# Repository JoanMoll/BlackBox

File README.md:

# BlackBox — Room Health / Environmental Monitoring PCB

Custom KiCad PCB for a battery-powered, ESP32-class device intended to monitor room/environment conditions and log data locally.

## Design previews

### 3D view

### PCB layout

### Schematic

## Project overview
BlackBox is a hardware design project focused on a practical embedded system that combines sensing, local storage, battery operation, and an ESP32-class MCU. The goal is a compact “room health” monitoring unit that can collect measurements and store them for later analysis.

## Intended system (high-level)
- MCU / Wireless: ESP32-class microcontroller (e.g., ESP32-S3)
- Sensors: LDR (ambient light), ultrasonic (distance/proximity), plus analog sensor input(s)
- Analog front-end: LMV321 op-amp stage for signal conditioning/amplification
- Storage: micro-SD card for local data logging
- Power: battery input (VBAT) with 3.3 V regulation and battery management/protection

## Repository contents
- KiCad project: `.kicad_pro`
- Schematic: `.kicad_sch`
- PCB layout: `.kicad_pcb`
- 3D model export: `.step` (if included)
- Documentation images: `docs/pcb_3d.png`, `docs/pcb_layout.png`, `docs/schematic.png`

## How to open and review
1. Install KiCad (v7+ recommended).
2. Open the `.kicad_pro` file.
3. Review the schematic (`.kicad_sch`) and PCB layout (`.kicad_pcb`).
4. Run ERC (schematic checks) and DRC (PCB checks) inside KiCad.

## Status
- Schematic and PCB layout created
- Next: final DRC/ERC pass and documentation polish
- Next: order PCB and bring-up tests (power rails, SD, sensor IO)
- Next: firmware (sampling + logging format) and enclosure design

## Skills demonstrated
- End-to-end PCB design workflow in KiCad (schematic capture, layout, manufacturable design)
- Embedded hardware system design (power, sensing, analog conditioning, storage interfaces)
- Clear engineering documentation for review (renders + structured project summary)

## License
If no license file is included, all rights reserved (portfolio viewing only).

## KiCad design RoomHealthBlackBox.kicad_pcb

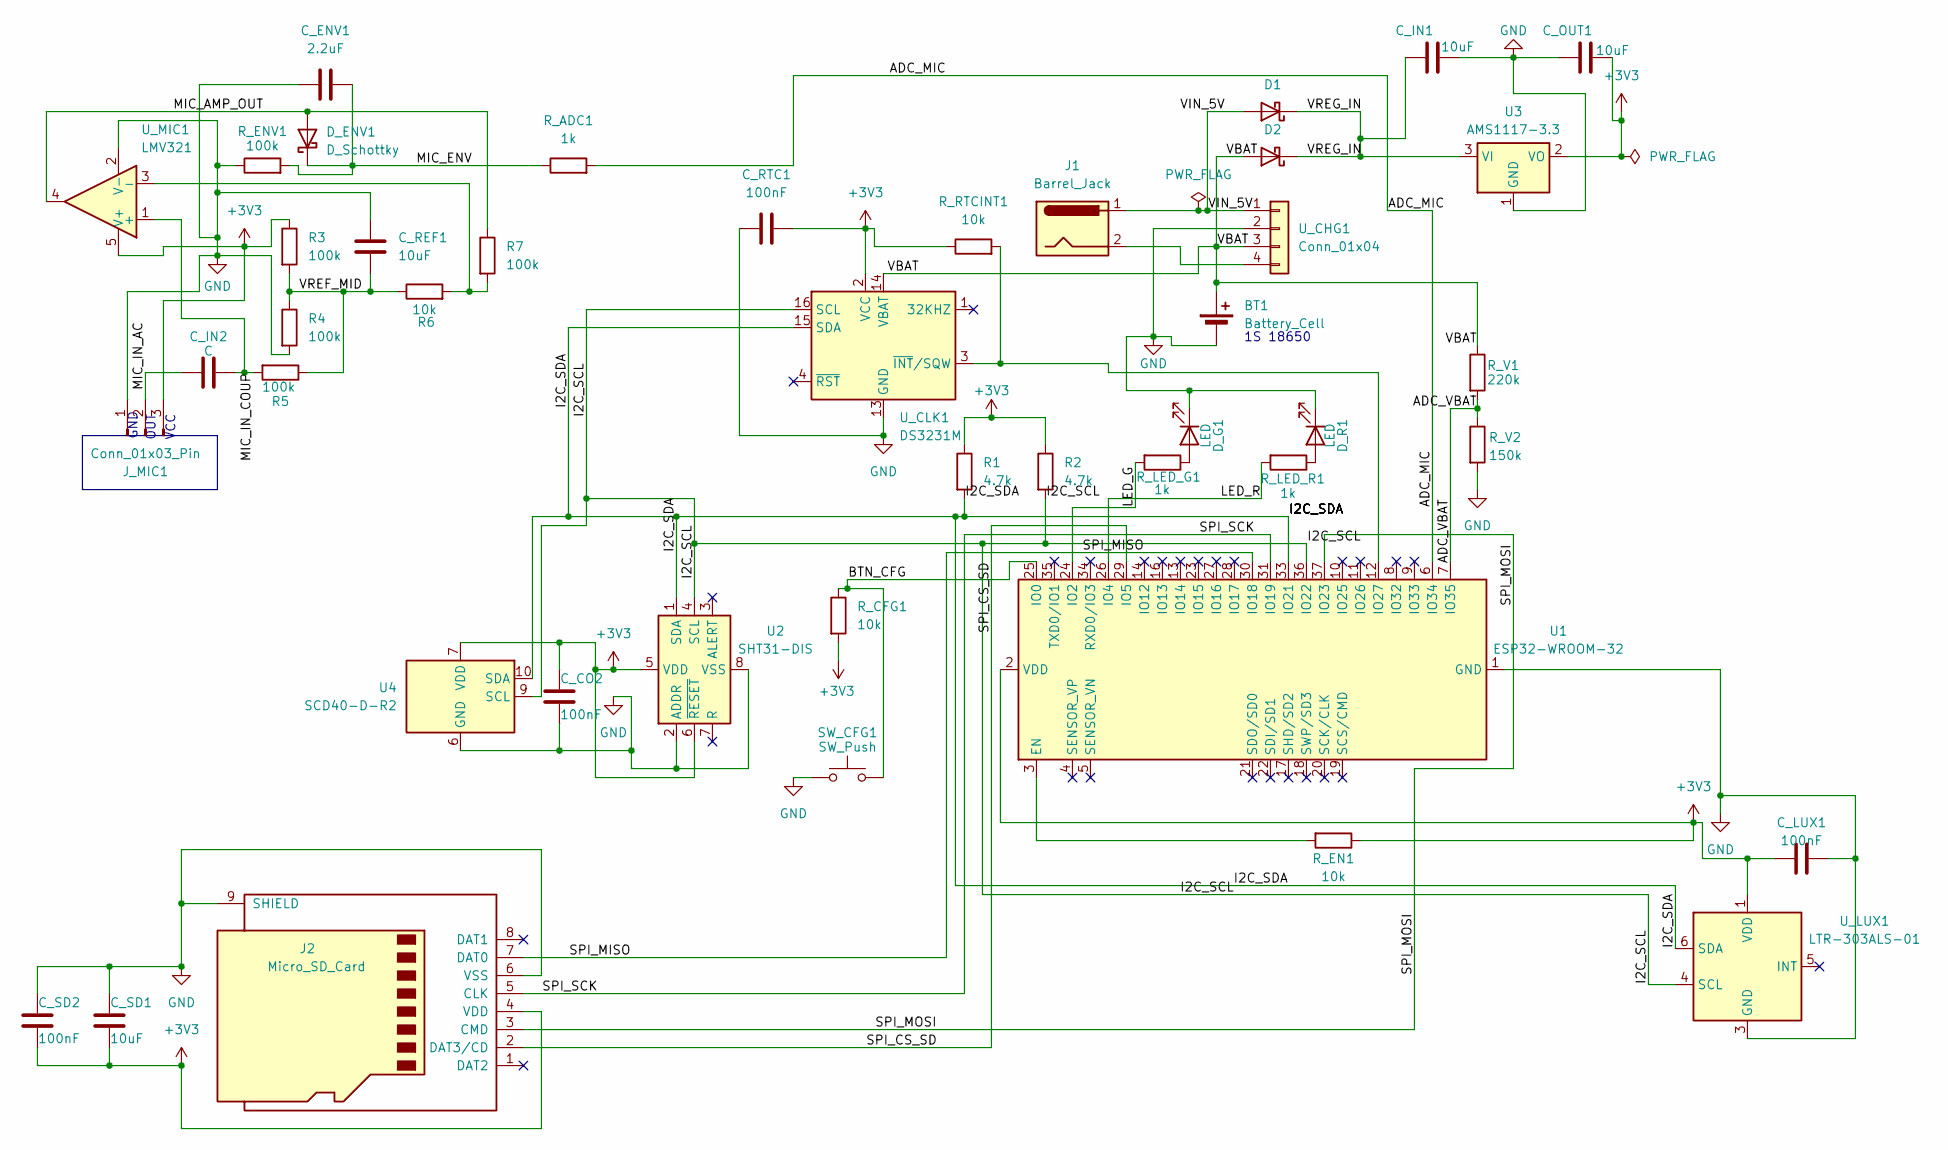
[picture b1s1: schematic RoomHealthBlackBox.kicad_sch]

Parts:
BT1: Battery_Cell; BatteryHolder_MPD_BH-18650-PC
C_CO2: 100nF; C_0201_0603Metric
C_ENV1: 2.2uF; C_0201_0603Metric
C_IN1: 10uF; C_0201_0603Metric
C_IN2: C; C_0201_0603Metric
C_LUX1: 100nF; C_0201_0603Metric
C_OUT1: 10uF; C_0201_0603Metric
C_REF1: 10uF; C_0201_0603Metric
C_RTC1: 100nF; C_0201_0603Metric
C_SD1: 10uF; C_0201_0603Metric
C_SD2: 100nF; C_0201_0603Metric
D1, D2: D_Schottky; D_0201_0603Metric
D_ENV1: D_Schottky; D_0201_0603Metric
D_G1: LED; LED_0201_0603Metric
D_R1: LED; LED_0201_0603Metric
J1: Barrel_Jack; BarrelJack_Horizontal
J2: Micro_SD_Card; microSD_HC_Molex_104031-0811
J_MIC1: Conn_01x03_Pin; PinHeader_1x04_P2.54mm_Vertical
R1, R2: 4.7k; R_0201_0603Metric
R3, R4, R5, R7: 100k; R_0201_0603Metric
R6: 10k; R_0201_0603Metric
R_ADC1: 1k; R_0201_0603Metric
R_CFG1: 10k; R_0201_0603Metric
R_EN1: 10k; R_0201_0603Metric
R_ENV1: 100k; R_0201_0603Metric
R_LED_G1: 1k; R_0201_0603Metric
R_LED_R1: 1k; R_0201_0603Metric
R_RTCINT1: 10k; R_0201_0603Metric
R_V1: 220k; R_0201_0603Metric
R_V2: 150k; R_0201_0603Metric
SW_CFG1: SW_Push; SW_SPST_PTS645Sx43SMTR92
U1: ESP32-WROOM-32
U2: SHT31-DIS; Sensirion_DFN-8-1EP_2.5x2.5mm_P0.5mm_EP1.1x1.7mm
U3: AMS1117-3.3; SOT-223-3_TabPin2
U4: SCD40-D-R2; Sensirion_SCD4x-1EP_10.1x10.1mm_P1.25mm_EP4.8x4.8mm
U_CHG1: Conn_01x04; PinHeader_1x04_P2.54mm_Vertical
U_CLK1: DS3231M; SOIC-16W_7.5x10.3mm_P1.27mm
U_LUX1: LTR-303ALS-01; Lite-On_LTR-303ALS-01
U_MIC1: LMV321; SOT-23-5

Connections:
+3V3: C_CO2.1, C_LUX1.1, C_OUT1.2, C_RTC1.2, C_SD1.2, C_SD2.2, J2.4 (VDD), J_MIC1.3, R1.1, R2.1, R3.1, R_CFG1.2, R_EN1.1, R_RTCINT1.1, U1.2 (VDD), U2.5 (VDD), U2.6 (~RESET), U3.2 (VO), U4.7 (VDD), U4.19 (VDD), U_CLK1.2 (VCC), U_LUX1.1 (VDD), U_MIC1.5 (V+)
/ADC_MIC: R_ADC1.2, U1.6 (IO34)
/ADC_VBAT: R_V1.2, R_V2.1, U1.7 (IO35)
/BTN_CFG: R_CFG1.1, SW_CFG1.2, U1.25 (IO0)
/I2C_SCL: R2.2, U1.36 (IO22), U2.4 (SCL), U4.9 (SCL), U_CLK1.16 (SCL), U_LUX1.4 (SCL)
/I2C_SDA: R1.2, U1.33 (IO21), U2.1 (SDA), U4.10 (SDA), U_CLK1.15 (SDA), U_LUX1.6 (SDA)
/LED_G: R_LED_G1.2, U1.24 (IO2)
/LED_R: R_LED_R1.2, U1.26 (IO4)
/MIC_AMP_OUT: D_ENV1.2 (A), R7.1, U_MIC1.4
/MIC_ENV: C_ENV1.2, D_ENV1.1 (K), R_ADC1.1, R_ENV1.2
/MIC_IN_AC: C_IN2.2, J_MIC1.2
/MIC_IN_COUP: C_IN2.1, R5.2, U_MIC1.1 (+)
/SPI_CS_SD: J2.2 (DAT3/CD), U1.29 (IO5)
/SPI_MISO: J2.7 (DAT0), U1.30 (IO18)
/SPI_MOSI: J2.3 (CMD), U1.37 (IO23)
/SPI_SCK: J2.5 (CLK), U1.31 (IO19)
/VBAT: BT1.1 (+), D2.2 (A), R_V1.1, U_CHG1.3, U_CLK1.14 (VBAT)
/VIN_5V: D1.2 (A), J1.1, U_CHG1.1
/VREF_MID: C_REF1.2, R3.2, R4.1, R5.1, R6.1
/VREG_IN: C_IN1.2, D1.1 (K), D2.1 (K), U3.3 (VI)
GND: BT1.2 (-), C_CO2.2, C_ENV1.1, C_IN1.1, C_LUX1.2, C_OUT1.1, C_REF1.1, C_RTC1.1, C_SD1.1, C_SD2.1, D_G1.1 (K), D_R1.1 (K), J2.6 (VSS), J2.9 (SHIELD), J_MIC1.1, R4.2, R_ENV1.1, R_V2.2, SW_CFG1.1, U1.1 (GND), U1.15 (GND), U1.38 (GND), U1.39 (GND), U2.2 (ADDR), U2.8 (VSS), U2.9 (VSS), U3.1 (GND), U4.6 (GND), U4.20 (GND), U4.21 (GND), U_CHG1.2, U_CLK1.5 (GND), U_CLK1.6 (GND), U_CLK1.7 (GND), U_CLK1.8 (GND), U_CLK1.9 (GND), U_CLK1.10 (GND), U_CLK1.11 (GND), U_CLK1.12 (GND), U_CLK1.13 (GND), U_LUX1.3 (GND), U_MIC1.2 (V-)
unnamed: D_G1.2 (A), R_LED_G1.1
unnamed: D_R1.2 (A), R_LED_R1.1
unnamed: R_EN1.2, U1.3 (EN)
unnamed: R_RTCINT1.2, U1.12 (IO27), U_CLK1.3 (~INT/SQW)
unnamed: J1.2, U_CHG1.4
unnamed: R6.2, R7.2, U_MIC1.3 (-)

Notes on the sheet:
OUT
GND
1S 18650
VCC

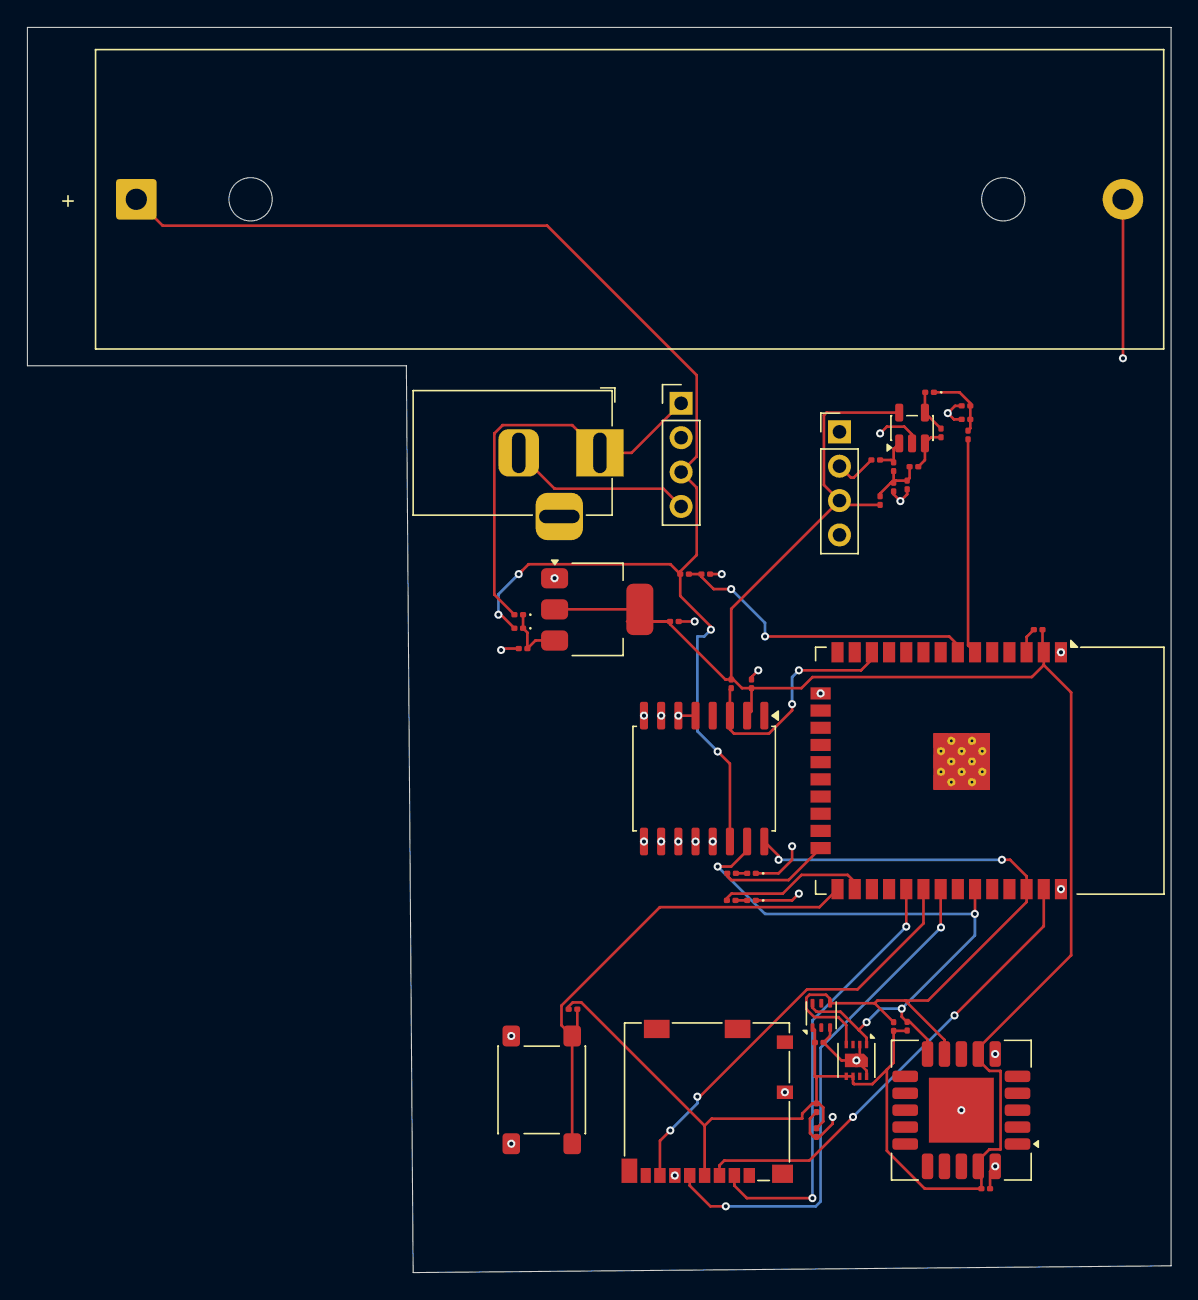
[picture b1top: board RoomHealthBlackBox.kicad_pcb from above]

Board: 2 copper layers, 84.5 x 92.0 mm, 44 parts (0 on the bottom side), 27 nets.

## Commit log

2026-02-19 Create README for BlackBox environmental monitoring device
    Added README.md with project overview and details.
2026-02-19 Clean repo structure: docs and fab, remove backups
2026-02-19 Remove backups, png exports, and report
2026-02-19 Revise README for clarity and add design previews
    Updated the README to improve clarity and added design previews.
2026-02-19 Update PCB images in README
    Updated image references in the README to new files.
